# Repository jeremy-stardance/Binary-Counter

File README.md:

# Binary-Counter
Week 4 of Hack Club Half-Life

This project should be able to count up when a button is pressed. Using my code and an arduino pro micro, the button should trigger the LED display of 6 LEDs to display the binary.

It will count up every 250 milliseconds when held.

# Circuit Design

The design uses resistors it ensure the LEDs keep working.

# Bill of Materials

| Component | Quantity | Cost ($) |
|---|---:|---:|
| Arduino Pro Micro | 1 | 9.33 |
| LEDs | 1 | 6.68 |
| Breadboard & Jumper Wires | 1 | 12.44|

I am hoping the jumper wires in the kit will be enough.

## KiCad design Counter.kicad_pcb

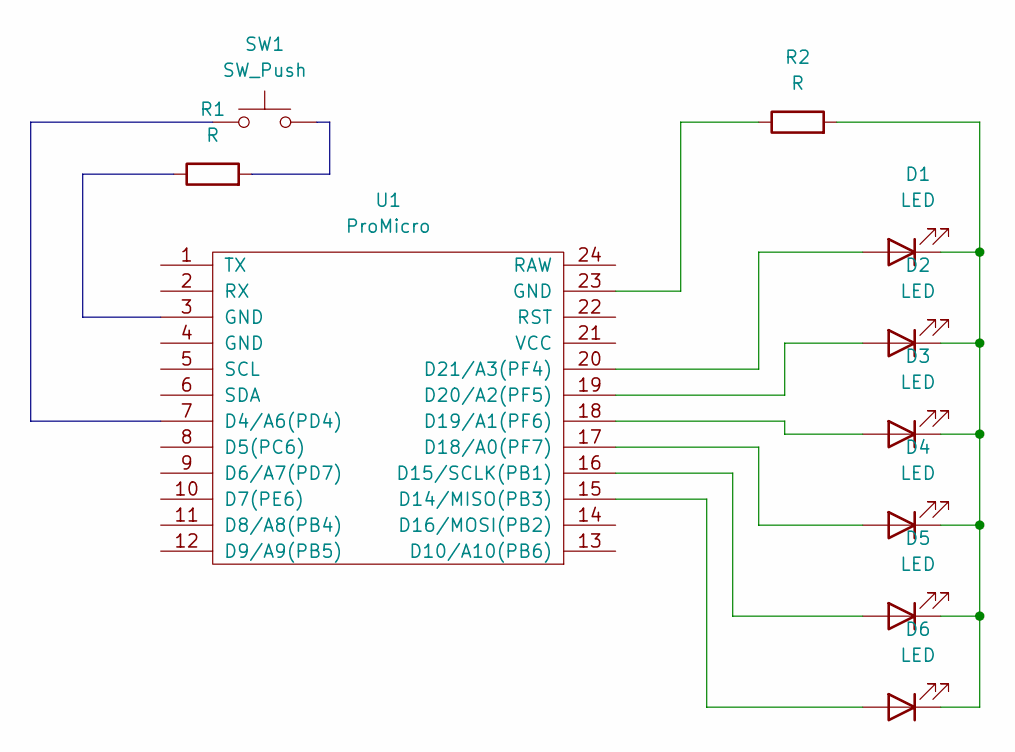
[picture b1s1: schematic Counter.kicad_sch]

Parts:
D1, D2, D3, D4, D5, D6: LED; LED_D5.0mm
R1, R2: R; R_0201_0603Metric
SW1: SW_Push; SW_Cherry_MX_1.00u_PCB
U1: ProMicro

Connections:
unnamed: D1.2 (A), U1.20 (D21/A3(PF4))
unnamed: D1.1 (K), D2.1 (K), D3.1 (K), D4.1 (K), D5.1 (K), D6.1 (K), R2.2
unnamed: D2.2 (A), U1.19 (D20/A2(PF5))
unnamed: D3.2 (A), U1.18 (D19/A1(PF6))
unnamed: D4.2 (A), U1.17 (D18/A0(PF7))
unnamed: D5.2 (A), U1.16 (D15/SCLK(PB1))
unnamed: D6.2 (A), U1.15 (D14/MISO(PB3))
unnamed: R1.1, U1.3 (GND)
unnamed: R1.2, SW1.2
unnamed: R2.1, U1.23 (GND)
unnamed: SW1.1, U1.7 (D4/A6(PD4))

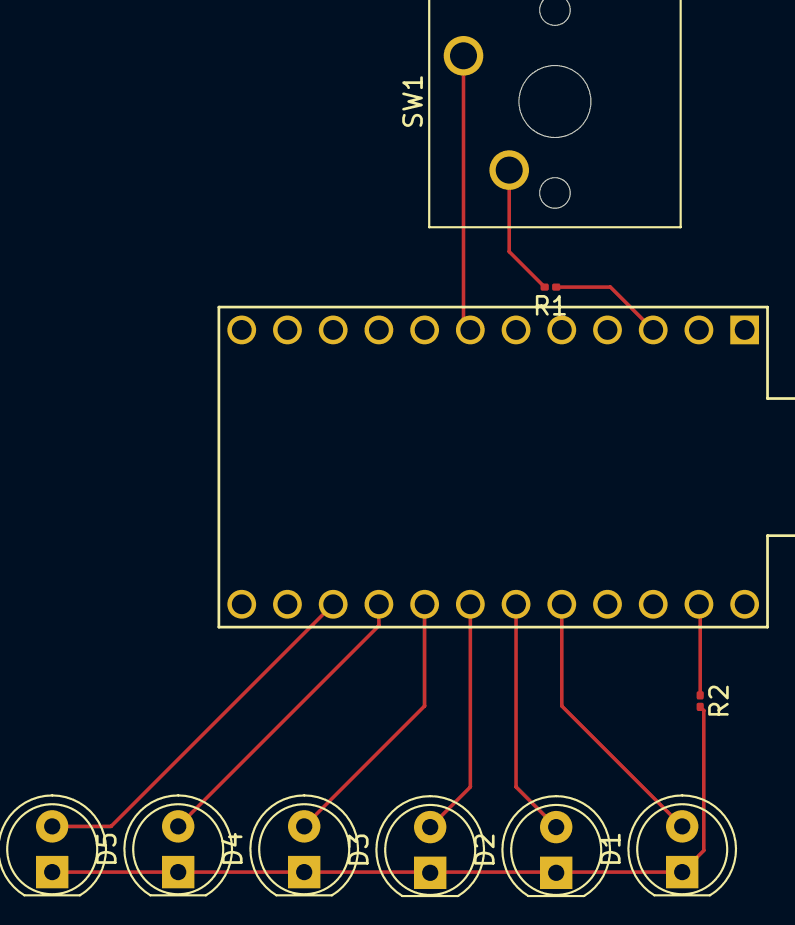
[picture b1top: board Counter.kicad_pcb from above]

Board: 2 copper layers, 10 parts (0 on the bottom side), 11 nets.
